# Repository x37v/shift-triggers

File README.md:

# shift-triggers

This is a kicad pcb/schematic project for driving modular synthesizer triggers with a few pins on a microcontroller using a shift register.

It provides 16 trigger outputs, an optional 3v->5v set of inputs, and the ability to cascade several boards.

It uses an MTA style connector for power, and should be able to be driven by 12 or 15v, probably even 9.

<a href="https://oshpark.com/shared_projects/Jd7M4dvT"></img></a>

## License

<br /><span xmlns:dct="http://purl.org/dc/terms/" property="dct:title">shift-triggers</span> by <a xmlns:cc="http://creativecommons.org/ns#" href="https://github.com/x37v/shift-triggers" property="cc:attributionName" rel="cc:attributionURL">Alex Norman</a> is licensed under a <a rel="license" href="http://creativecommons.org/licenses/by/4.0/">Creative Commons Attribution 4.0 International License</a>.<br />Based on a work at <a xmlns:dct="http://purl.org/dc/terms/" href="https://github.com/pichenettes/eurorack/tree/master/grids/hardware_design" rel="dct:source">https://github.com/pichenettes/eurorack/tree/master/grids/hardware_design</a>.

## Thanks

Thanks to [Mutable Instruments](https://mutable-instruments.net) for providing example schematics.
I modeled these triggers off the [Grids](https://mutable-instruments.net/modules/grids/)
[schematic](https://github.com/pichenettes/eurorack/tree/master/grids/hardware_design).

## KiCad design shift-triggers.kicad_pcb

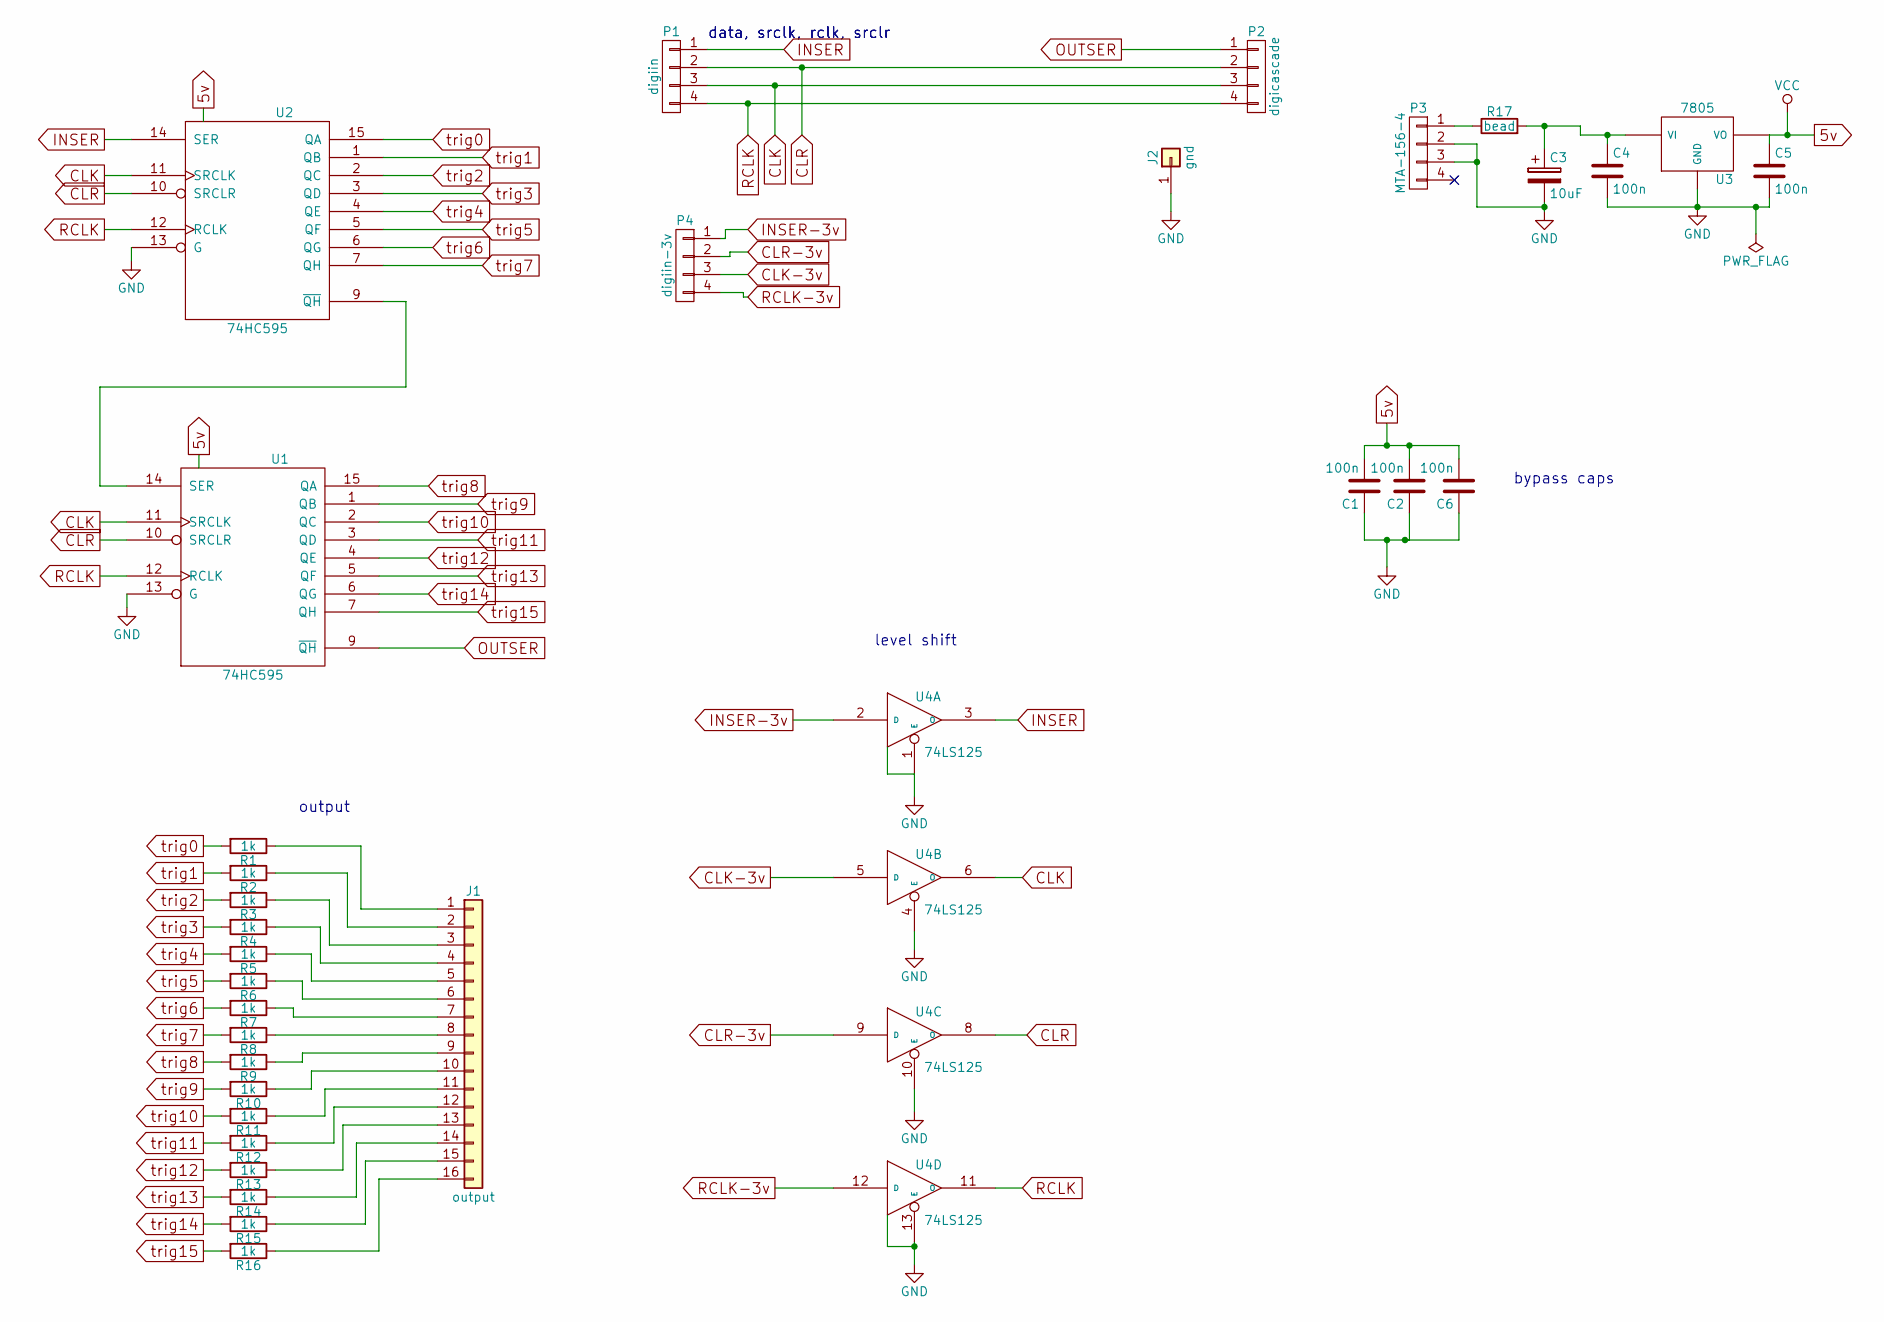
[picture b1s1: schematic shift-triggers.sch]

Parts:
C1, C2, C6: 100n; C_Disc_D3.4mm_W2.1mm_P2.50mm
C3: 10uF; CP_Radial_D7.5mm_P2.50mm
C4, C5: 100n; C_Disc_D4.3mm_W1.9mm_P5.00mm
J1: output; Pin_Header_Straight_1x16_Pitch2.54mm
J2: gnd; Pin_Header_Straight_1x01_Pitch2.54mm
P1: digiin; Pin_Header_Straight_1x04_Pitch2.54mm
P2: digicascade; Pin_Header_Straight_1x04_Pitch2.54mm
P3: MTA-156-4
P4: digiin-3v; Pin_Header_Straight_1x04_Pitch2.54mm
R1, R2, R3, R4, R5, R6, R7, R8, R9, R10, R11, R12, R13, R14, R15, R16: 1k; R_Axial_DIN0204_L3.6mm_D1.6mm_P7.62mm_Horizontal
R17: bead; R_Axial_DIN0207_L6.3mm_D2.5mm_P10.16mm_Horizontal
U1, U2: 74HC595; DIP-16_W7.62mm_LongPads
U3: 7805; TO-220_Vertical
U4: 74LS125; DIP-14_W7.62mm_LongPads

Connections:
5v: C1.2, C2.2, C5.1, C6.2, U1.16 (VCC), U2.16 (VCC), U3.3 (VO), U4.14 (VCC)
CLK: P1.3, P2.3, U1.11 (SRCLK), U2.11 (SRCLK), U4.6 (O); also elsewhere on the board
CLK-3v: P4.3, U4.5 (D); also elsewhere on the board
CLR: P1.2, P2.2, U1.10 (SRCLR), U2.10 (SRCLR), U4.8 (O); also elsewhere on the board
CLR-3v: P4.2, U4.9 (D); also elsewhere on the board
GND: C1.1, C2.1, C3.2, C4.2, C5.2, C6.1, J2.1, P3.2, P3.3, U1.8 (GND), U1.13 (G), U2.8 (GND), U2.13 (G), U3.2 (GND), U4.1 (E), U4.4 (E), U4.7 (GND), U4.10 (E), U4.13 (E); also elsewhere on the board
INSER: P1.1, U2.14 (SER), U4.3 (O); also elsewhere on the board
INSER-3v: P4.1, U4.2 (D); also elsewhere on the board
unnamed: C3.1, C4.1, R17.2, U3.1 (VI)
unnamed: J1.1, R1.1
unnamed: J1.2, R2.1
unnamed: J1.3, R3.1
unnamed: J1.4, R4.1
unnamed: J1.5, R5.1
unnamed: J1.6, R6.1
unnamed: J1.7, R7.1
unnamed: J1.8, R8.1
unnamed: J1.9, R9.1
unnamed: J1.10, R10.1
unnamed: J1.11, R11.1
unnamed: J1.12, R12.1
unnamed: J1.13, R13.1
unnamed: J1.14, R14.1
unnamed: J1.15, R15.1
unnamed: J1.16, R16.1
unnamed: P3.1, R17.1
unnamed: U1.14 (SER), U2.9 (~QH)
OUTSER: P2.1, U1.9 (~QH)
RCLK: P1.4, P2.4, U1.12 (RCLK), U2.12 (RCLK), U4.11 (O); also elsewhere on the board
RCLK-3v: P4.4, U4.12 (D); also elsewhere on the board
trig0: R1.2, U2.15 (QA)
trig1: R2.2, U2.1 (QB)
trig2: R3.2, U2.2 (QC)
trig3: R4.2, U2.3 (QD)
trig4: R5.2, U2.4 (QE)
trig5: R6.2, U2.5 (QF)
trig6: R7.2, U2.6 (QG)
trig7: R8.2, U2.7 (QH)
trig8: R9.2, U1.15 (QA)
trig9: R10.2, U1.1 (QB)
trig10: R11.2, U1.2 (QC)
trig11: R12.2, U1.3 (QD)
trig12: R13.2, U1.4 (QE)
trig13: R14.2, U1.5 (QF)
trig14: R15.2, U1.6 (QG)
trig15: R16.2, U1.7 (QH)

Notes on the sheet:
data, srclk, rclk, srclr
bypass caps
level shift
output

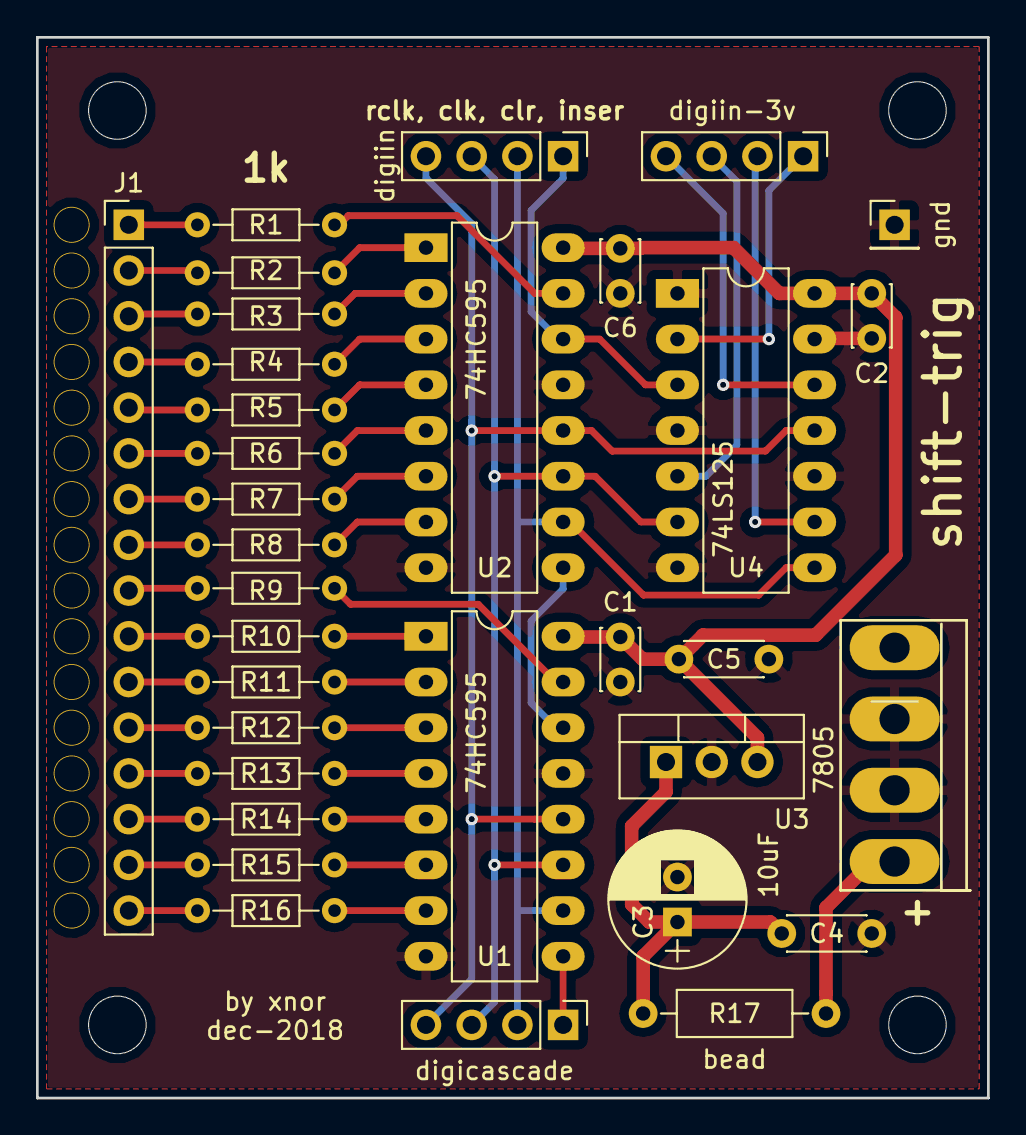
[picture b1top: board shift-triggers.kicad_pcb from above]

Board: 2 copper layers, 52.8 x 58.9 mm, 37 parts (0 on the bottom side), 46 nets.

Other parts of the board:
GND: gnd; Pin_Header_Straight_1x01_Pitch2.54mm
IN-3v: digiin-3v; Pin_Header_Straight_1x04_Pitch2.54mm
IN-5v: digiin; Pin_Header_Straight_1x04_Pitch2.54mm
REF1, REF2, REF3, REF4: MountingHole_3.2mm_M3

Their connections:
CLK: IN-5v.3; also elsewhere on the board
CLK-3v: IN-3v.3; also elsewhere on the board
CLR: IN-5v.2; also elsewhere on the board
CLR-3v: IN-3v.2; also elsewhere on the board
GND: GND.1; also elsewhere on the board
INSER: IN-5v.1; also elsewhere on the board
INSER-3v: IN-3v.1; also elsewhere on the board
RCLK: IN-5v.4; also elsewhere on the board
RCLK-3v: IN-3v.4; also elsewhere on the board

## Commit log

2018-12-22 initial schematic and pcb
2018-12-22 added ground, updated packages
2018-12-22 more dialed in layout
2018-12-22 mostly layed out now
2018-12-22 finalized pcb?
2018-12-22 readme
2018-12-22 spacing
2018-12-22 thanks
2018-12-22 updated link style
2018-12-22 added license
2018-12-22 license info
2018-12-22 moved thanks
2018-12-22 oshpark
